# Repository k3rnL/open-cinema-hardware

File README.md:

# Open Cinema Hardware

Editable hardware for [Open Cinema](https://github.com/k3rnL/open-cinema). The [resources repository](https://github.com/k3rnL/open-cinema-resources) holds searchable knowledge and decision history.

## Current work: A12 routed ARC prototype

[Open A12](boards/rear-io-A12/README.md). ADV7511 ARC candidate → CS8416 four-source selector → three-pair LVDS link → Raspberry Pi. The Pi decodes/processes audio and sends output over USB to the amplifier. Optical ×2, coax, HDMI and six speaker pairs remain on one horizontal board.

- [Editable KiCad project](boards/rear-io-A12/rear-io-A12.kicad_pro) and [routed PCB](boards/rear-io-A12/rear-io-A12.kicad_pcb)
- [Schematic PDF](boards/rear-io-A12/exports/rear-io-A12-schematic.pdf)
- [Rigid STEP](boards/rear-io-A12/exports/rear-io-A12-rigid.step) / [Fusion archive](boards/rear-io-A12/exports/rear-io-A12-rigid.f3d)
- [Manufacturing review files](boards/rear-io-A12/manufacturing-review/README.md), [sourcing](boards/rear-io-A12/sourcing.md), [requirements](boards/rear-io-A12/requirements.md), [verification](boards/rear-io-A12/verification.md)

**Routing is complete: 0 ERC violations, 0 DRC violations and 0 unrouted connections. Manufacturing release remains on hold.** ARC-only/CEC startup, DD+ payload preservation and Pi capture have not been demonstrated; ADV7511 eligible supply and horizontal KLS speaker-clip current rating remain unresolved. The package includes Gerbers, drills, BOM/CPL, stackup and a [qualification plan](boards/rear-io-A12/bring-up.md); it is not an approved order.

The [accepted ARC scope](docs/arc-v1-requirements.md) defers eARC/lossless return audio while retaining DD+ Atmos as a validation target. A12 does not claim those tests passed.

## Mechanical integration

A12 preserves the 228 ×39.8 ×1.6 mm PCB, connector positions and four Ø3 holes at installation x±110 mm, depths 12/30 mm. Its rigid files contain one component with 162 solids and no child components; both reimports match. No owner backplate, L brackets or mains circuit is included.

The latest owner opening is 250 ×51 mm. Assembled clearance, airflow, cable access, tolerances and loaded thermal/EMI behavior remain to be checked. Exports retain the component-down installation datum, nominal z 67 mm. Existing owner CAD and the linked `rear-io-A5-assembly` cloud document were not saved or overwritten. Git publication does not update Fusion links automatically.

## Previous revisions

- [A11 ARC electrical study](boards/rear-io-A11/README.md): historical unrouted schematic/placement.
- [A10 electrical draft](boards/rear-io-A10/README.md): historical mux/LVDS design, HDMI unwired.
- [A9 mechanical baseline](docs/pcb-only-assembly-A9.md), [A8 horizontal study](docs/horizontal-assembly-A8.md).
- [Original mechanical KiCad project](boards/rear-io/rear-io.kicad_pro): manual edits preserved.
- [A7 vertical design in history](https://github.com/k3rnL/open-cinema-hardware/tree/eae54aa79c94255bdad5aaae5bf087d2b4166b0e).

JLCPCB is preferred; Global Sourcing/pre-order and external suppliers are allowed. No purchase or supplier contact was made. The saved A12 board owns routing; do not regenerate over manual work. [Checks and export reproduction](boards/rear-io-A12/verification.md).

No project hardware license has been selected. KiCad assets retain their [attribution/license](docs/sources/README.md).

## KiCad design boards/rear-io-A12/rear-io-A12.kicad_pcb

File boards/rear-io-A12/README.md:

# Rear I/O A12 — routed ARC prototype

2026-11-04. **Routing complete; manufacturing release on hold for qualification.**

A12 routes the ADV7511 ARC candidate, CS8416 four-source selector and three-pair LVDS transmitter. Audio decoding and processing remain on the Pi, with USB output to the amplifier. It adds a TPD1E10B06DYAR coaxial ESD clamp and completes the passive/header reference selections. This is an editable prototype, not a demonstrated ARC/DD+ product.

- [KiCad project](rear-io-A12.kicad_pro), [schematic](rear-io-A12.kicad_sch), [routed PCB](rear-io-A12.kicad_pcb).
- [Schematic PDF](exports/rear-io-A12-schematic.pdf), [front copper](exports/routing-front.svg), [back copper](exports/routing-back.svg).
- [Rigid STEP](exports/rear-io-A12-rigid.step) / [Fusion archive](exports/rear-io-A12-rigid.f3d) for enclosure integration.
- [Manufacturing review package](manufacturing-review/README.md), [requirements](requirements.md), [sourcing](sourcing.md), [verification](verification.md), [bring-up and release gates](bring-up.md).

## Routing and checks

Four copper layers: signal/power on both outer layers, continuous inner ground in the electronics region, plus outer ground fills and thermal/return vias. All 12 BTL speaker conductors have independent 2.5 mm paths on both outer layers with through-hole endpoints and no intervening vias. No speaker negative is tied to ground.

Final KiCad checks: **0 ERC violations, 0 DRC violations, 0 unrouted connections**. Separate schematic and board review passes check 423 electrical pad keys, 98 footprints and 92 resolved model links. These are static checks by one assistant, not independent engineer approval or powered testing. [Exact results and hashes](exports/review-two-passes.json).

The 228 × 39.8 × 1.6 mm outline, external connector positions and four Ø3 mounting holes remain unchanged from A9. The 250 × 51 mm owner opening still needs an assembled clearance/airflow check. No backplate, L brackets or mains circuit is included.

## Fusion integration

The STEP and F3D each contain **one component with 162 solid bodies and no child components**. Both reimports match their exported geometry. They use the previous component-down installation datum, nominal seating z 67 mm. Insert the entire component and joint a PCB mounting hole; disable Ground to Parent if needed. These files are separate integration exports. The existing linked Fusion cloud component and the owner's enclosure were not overwritten or saved.

## Why ordering remains on hold

ADV7511 procurement eligibility and ARC-only/DD+ operation remain unresolved. CEC firmware, Pi HAT/capture, speaker-clip current rating/supply, thermal/EMI/ESD behavior and assembled tolerances need qualification. Some CAD is generic library geometry or project reconstruction; it is not a guarantee of vendor tolerances. The Gerbers/BOM/CPL are supplied for engineering and supplier review, with an explicit hold notice. No supplier was contacted and no order was placed.

A11 remains historical. The routed PCB is the editable layout authority; do not rerun the A11 placement generator over it. See [reproduction instructions](verification.md).

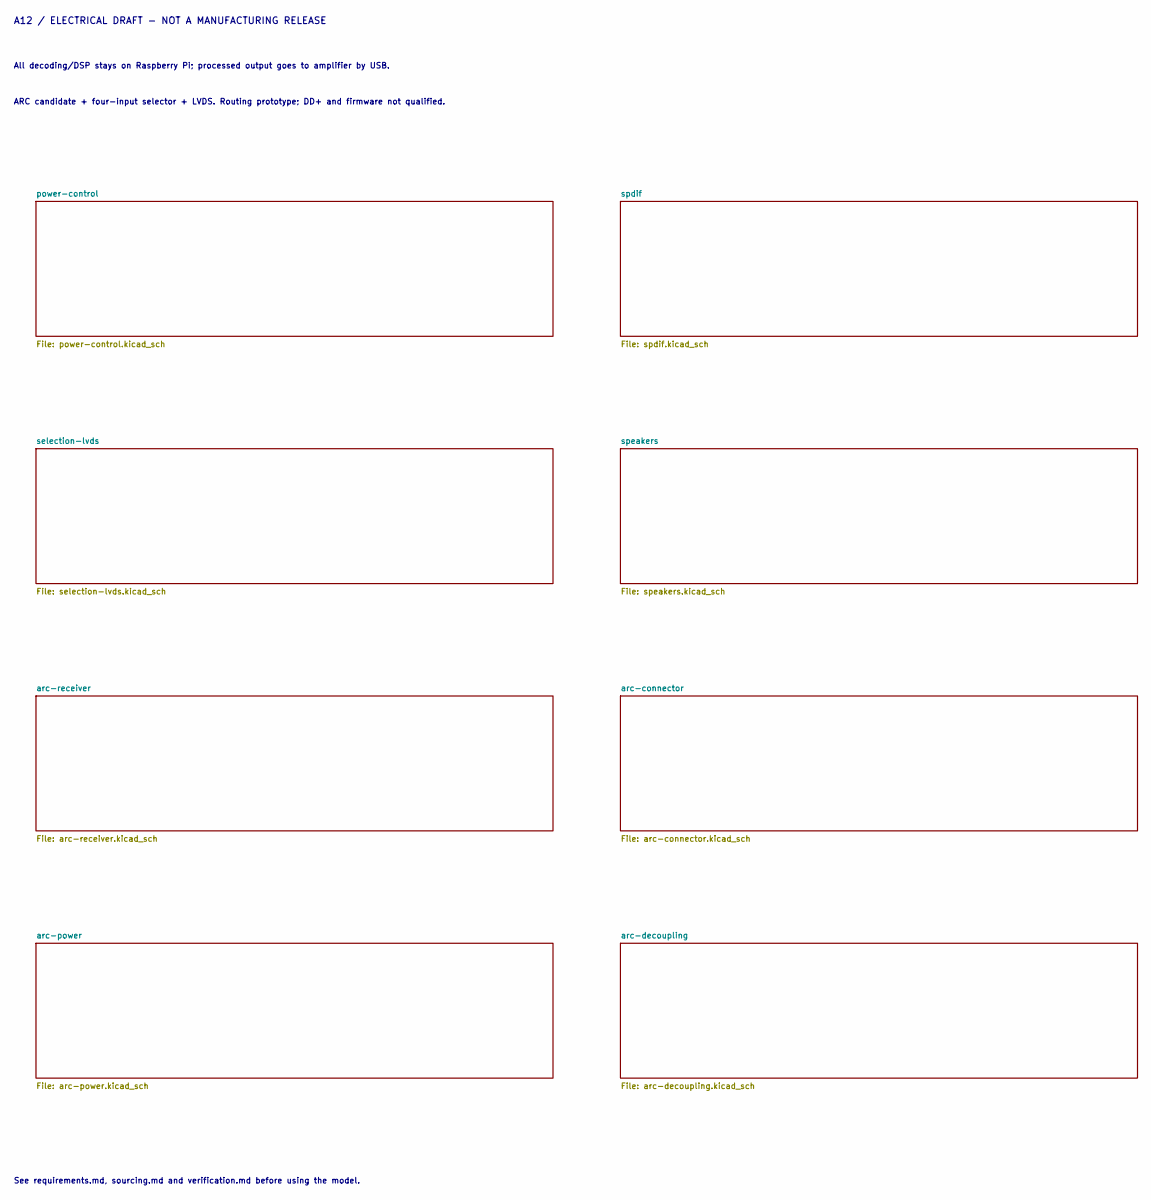
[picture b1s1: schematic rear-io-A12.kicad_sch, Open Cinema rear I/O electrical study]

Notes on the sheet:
A12 / ELECTRICAL DRAFT - NOT A MANUFACTURING RELEASE
All decoding/DSP stays on Raspberry Pi; processed output goes to amplifier by USB.
ARC candidate + four-input selector + LVDS. Routing prototype; DD+ and firmware not qualified.
See requirements.md, sourcing.md and verification.md before using the model.

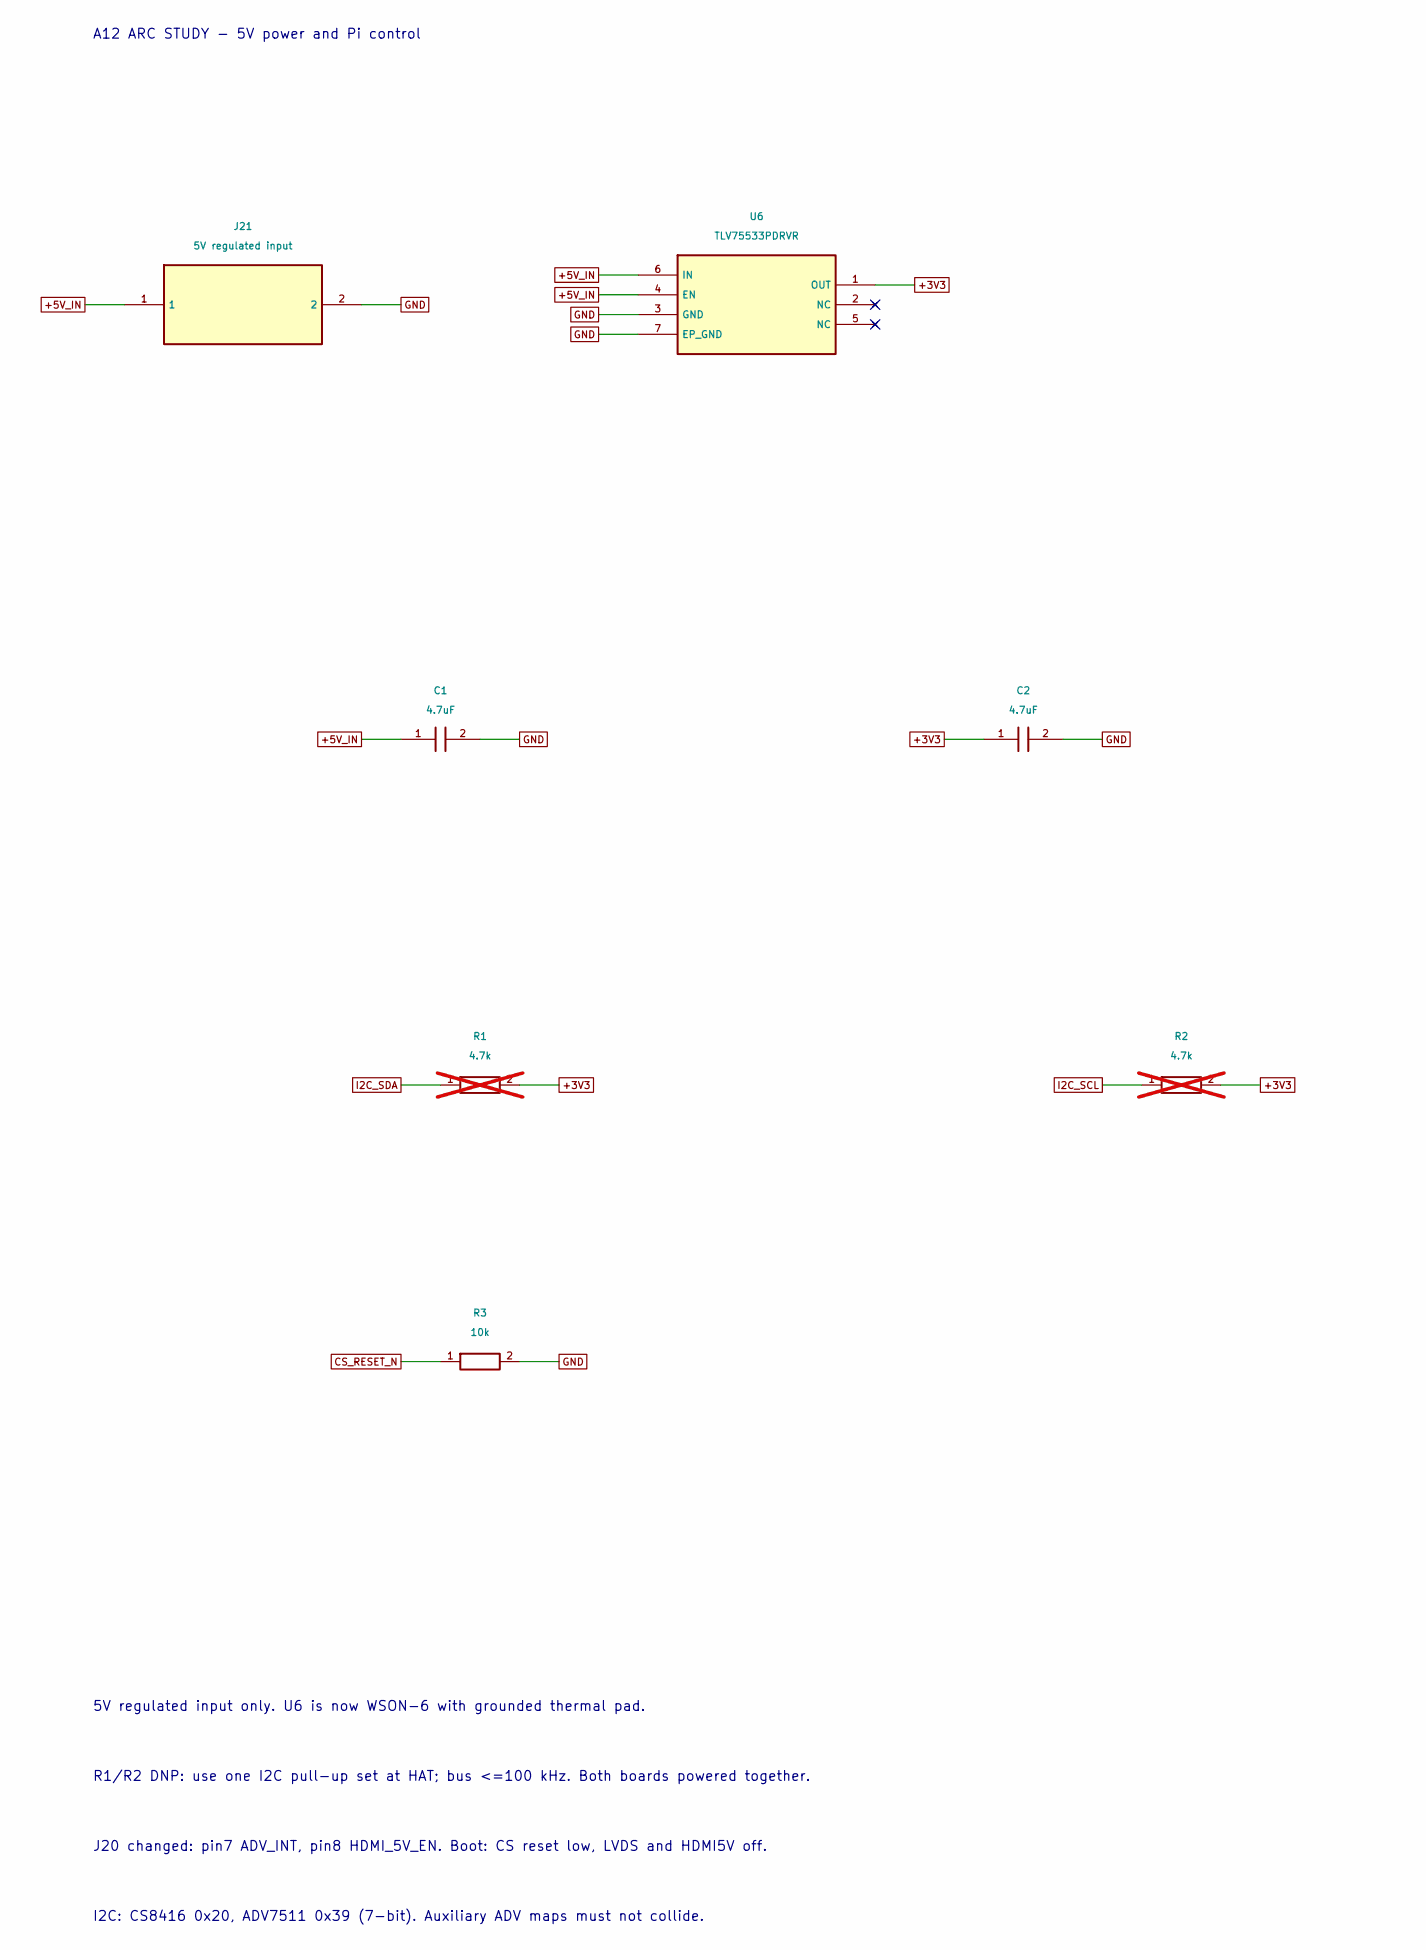
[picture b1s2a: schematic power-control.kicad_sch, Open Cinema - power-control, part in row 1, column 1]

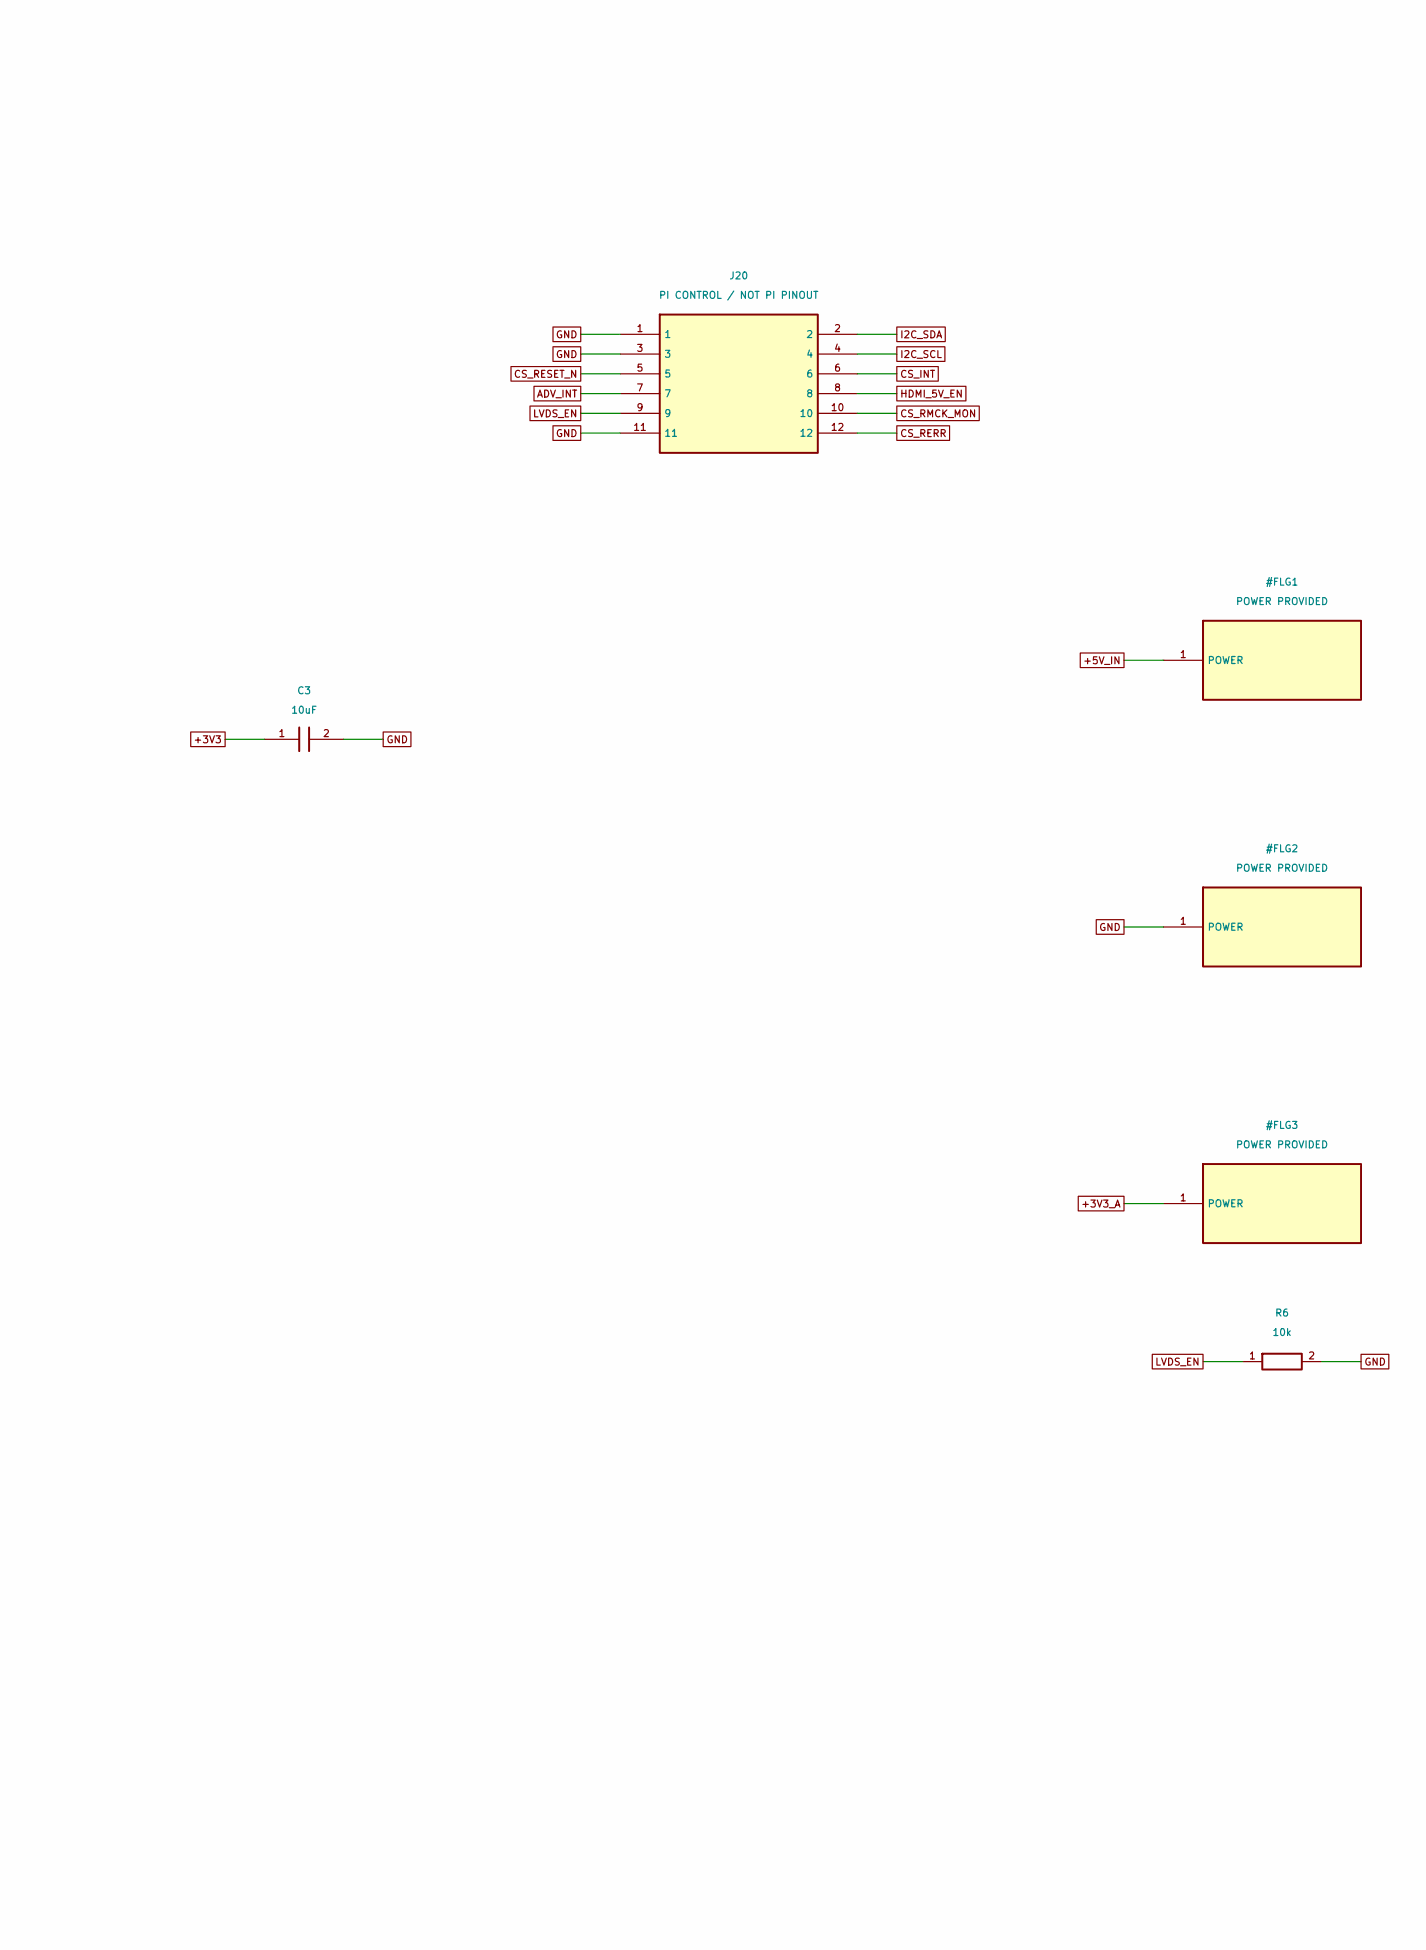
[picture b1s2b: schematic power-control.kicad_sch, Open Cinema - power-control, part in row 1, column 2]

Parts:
C1, C2: 4.7uF; C_0603_1608Metric; MPN CL10A475KO8NNNC
C3: 10uF; C_0603_1608Metric; MPN CL10A106KP8NNNC
J20: PI CONTROL / NOT PI PINOUT; PinHeader_2x06_P2.54mm_Vertical; MPN TSW-106-07-G-D
J21: 5V regulated input; PinHeader_1x02_P2.54mm_Vertical; MPN TSW-102-07-G-S
R1, R2: 4.7k; R_0603_1608Metric; MPN RC0603FR-074K7L; not fitted
R3, R6: 10k; R_0603_1608Metric; MPN RC0603FR-0710KL
U6: TLV75533PDRVR; WSON-6-1EP_2x2mm_P0.65mm_EP1x1.6mm; MPN TLV75533PDRVR

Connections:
+3V3: C2.1, C3.1, R1.2, R2.2, U6.1 (OUT); also elsewhere on the board
+5V_IN: C1.1, J21.1, U6.4 (EN), U6.6 (IN); also elsewhere on the board
ADV_INT: J20.7; also elsewhere on the board
CS_INT: J20.6; also elsewhere on the board
CS_RERR: J20.12; also elsewhere on the board
CS_RESET_N: J20.5, R3.1; also elsewhere on the board
CS_RMCK_MON: J20.10; also elsewhere on the board
GND: C1.2, C2.2, C3.2, J20.1, J20.3, J20.11, J21.2, R3.2, R6.2, U6.3 (GND), U6.7 (EP_GND); also elsewhere on the board
HDMI_5V_EN: J20.8; also elsewhere on the board
I2C_SCL: J20.4, R2.1; also elsewhere on the board
I2C_SDA: J20.2, R1.1; also elsewhere on the board
LVDS_EN: J20.9, R6.1; also elsewhere on the board

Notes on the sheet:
A12 ARC STUDY - 5V power and Pi control
5V regulated input only. U6 is now WSON-6 with grounded thermal pad.
R1/R2 DNP: use one I2C pull-up set at HAT; bus <=100 kHz. Both boards powered together.
J20 changed: pin7 ADV_INT, pin8 HDMI_5V_EN. Boot: CS reset low, LVDS and HDMI5V off.
I2C: CS8416 0x20, ADV7511 0x39 (7-bit). Auxiliary ADV maps must not collide.

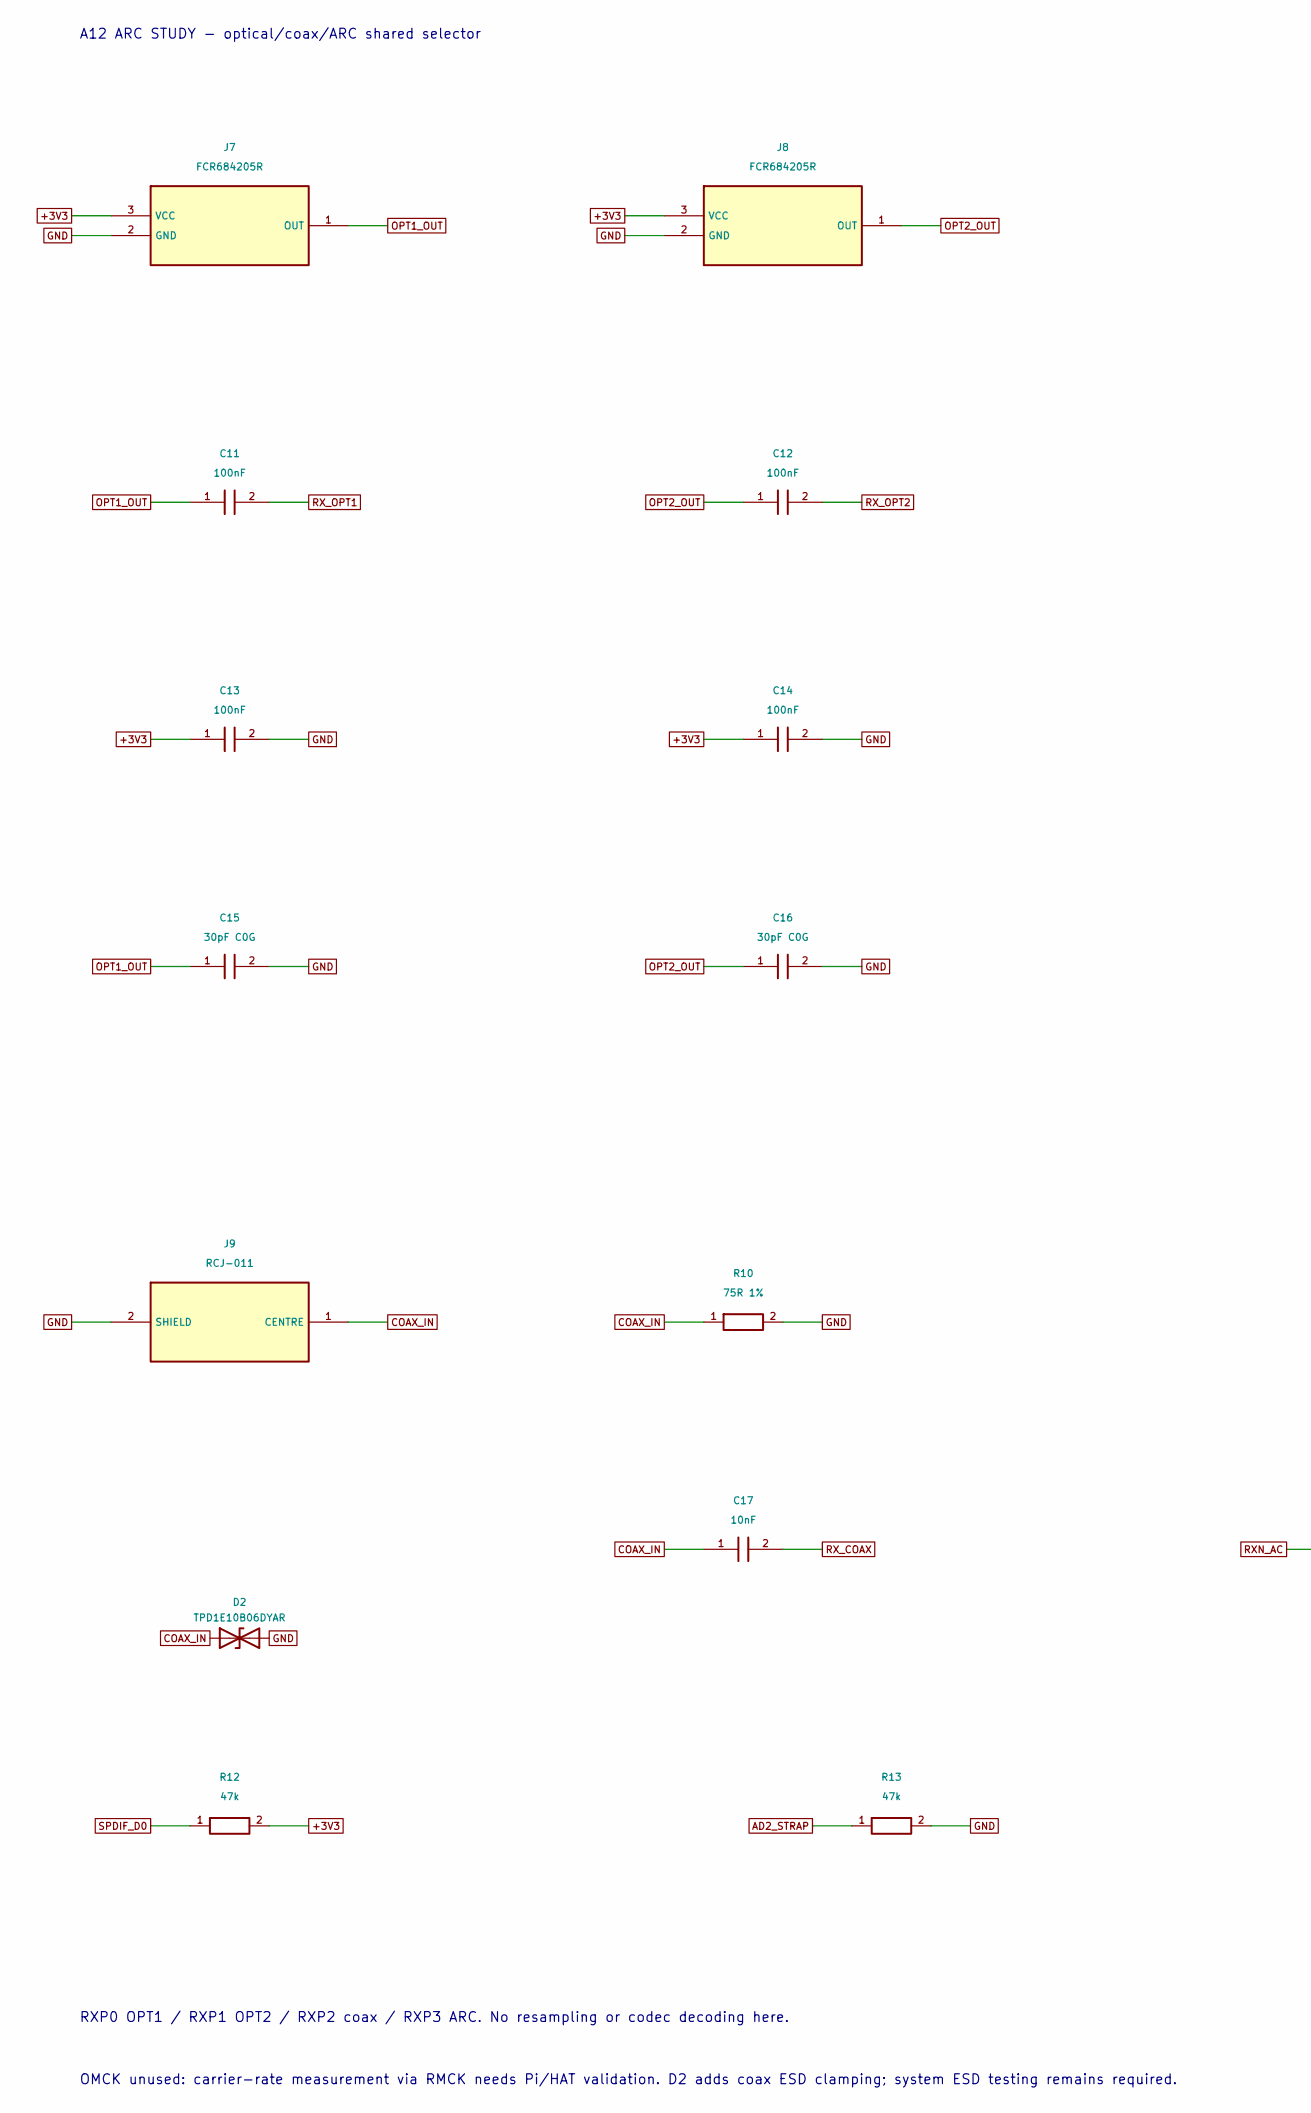
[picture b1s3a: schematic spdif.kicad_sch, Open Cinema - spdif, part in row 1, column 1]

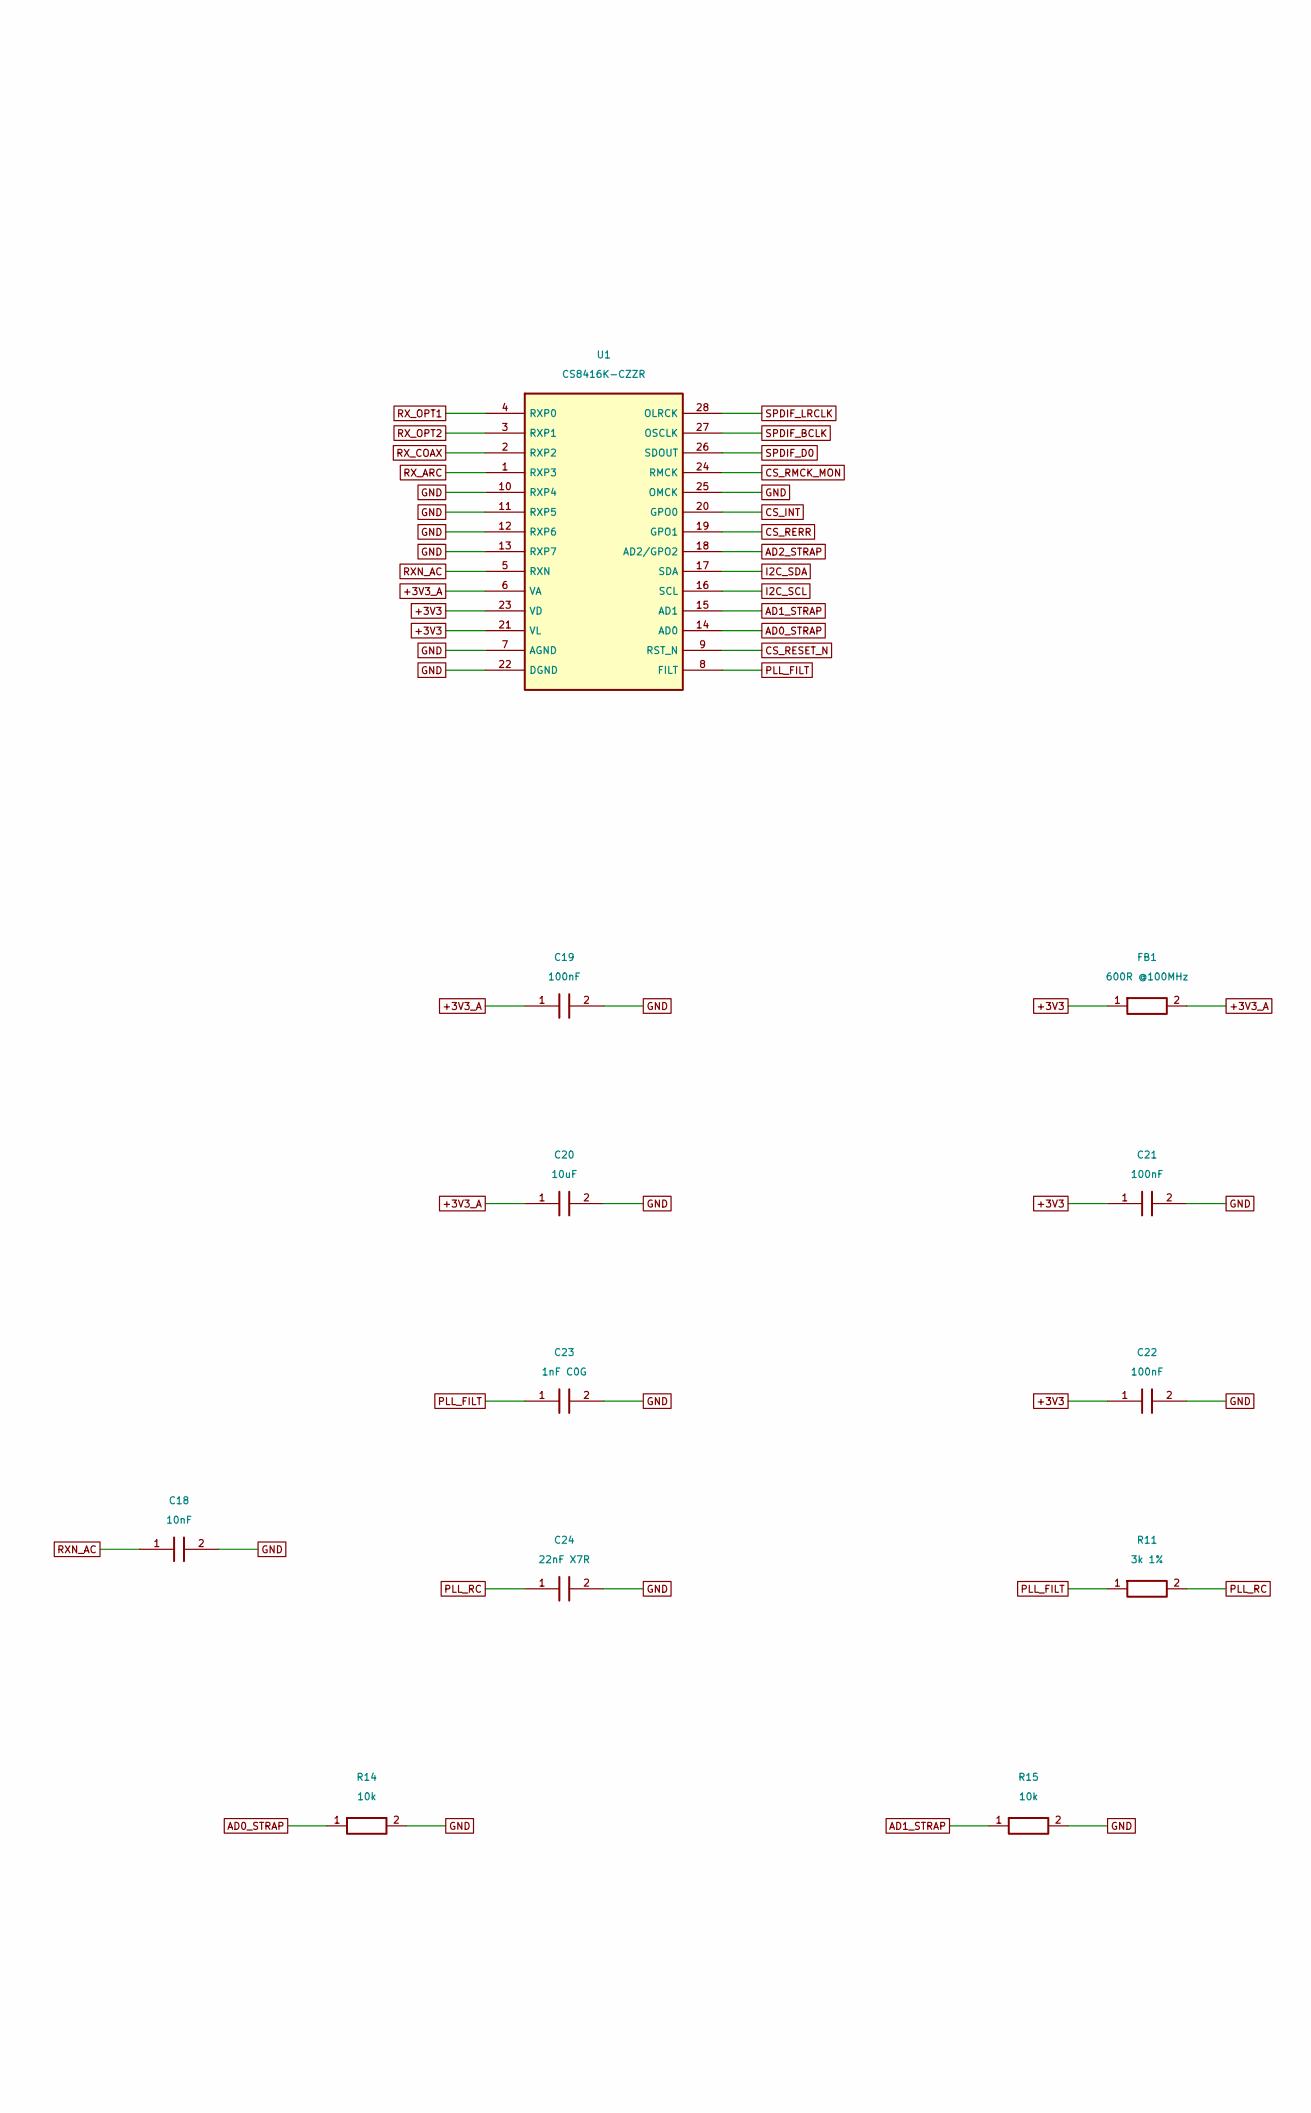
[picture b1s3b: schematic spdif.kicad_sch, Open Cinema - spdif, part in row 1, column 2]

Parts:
C11, C12, C13, C14, C19, C21, C22: 100nF; C_0603_1608Metric; MPN CL10B104KB8NNNC
C15, C16: 30pF C0G; C_0603_1608Metric; MPN CL10C300JB8NNNC
C17, C18: 10nF; C_0603_1608Metric; MPN CL10B103KB8NNNC
C20: 10uF; C_0603_1608Metric; MPN CL10A106KP8NNNC
C23: 1nF C0G; C_0603_1608Metric; MPN CL10C102JB8NNNC
C24: 22nF X7R; C_0603_1608Metric; MPN CL10B223KB8NNNC
D2: TPD1E10B06DYAR; D_SOD-523; MPN TPD1E10B06DYAR
FB1: 600R @100MHz; L_0603_1608Metric; MPN BLM18AG601SN1D
J7, J8: FCR684205R; Cliff_FCR684205R; MPN FCR684205R
J9: RCJ-011; SameSky_RCJ_011_Horizontal_A8; MPN RCJ-011
R10: 75R 1%; R_0603_1608Metric; MPN RC0603FR-0775RL
R11: 3k 1%; R_0603_1608Metric; MPN RC0603FR-073KL
R12, R13: 47k; R_0603_1608Metric; MPN RC0603FR-0747KL
R14, R15: 10k; R_0603_1608Metric; MPN RC0603FR-0710KL
U1: CS8416K-CZZR; TSSOP-28_4.4x9.7mm_P0.65mm; MPN CS8416K-CZZR

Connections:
+3V3: C13.1, C14.1, C21.1, C22.1, FB1.1, J7.3 (VCC), J8.3 (VCC), R12.2, U1.21 (VL), U1.23 (VD); also elsewhere on the board
+3V3_A: C19.1, C20.1, FB1.2, U1.6 (VA)
AD0_STRAP: R14.1, U1.14 (AD0)
AD1_STRAP: R15.1, U1.15 (AD1)
AD2_STRAP: R13.1, U1.18 (AD2/GPO2)
COAX_IN: C17.1, D2.1 (A1), J9.1 (CENTRE), R10.1
CS_INT: U1.20 (GPO0); also elsewhere on the board
CS_RERR: U1.19 (GPO1); also elsewhere on the board
CS_RESET_N: U1.9 (RST_N); also elsewhere on the board
CS_RMCK_MON: U1.24 (RMCK); also elsewhere on the board
GND: C13.2, C14.2, C15.2, C16.2, C18.2, C19.2, C20.2, C21.2, C22.2, C23.2, C24.2, D2.2 (A2), J7.2 (GND), J8.2 (GND), J9.2 (SHIELD), R10.2, R13.2, R14.2, R15.2, U1.7 (AGND), U1.10 (RXP4), U1.11 (RXP5), U1.12 (RXP6), U1.13 (RXP7), U1.22 (DGND), U1.25 (OMCK); also elsewhere on the board
I2C_SCL: U1.16 (SCL); also elsewhere on the board
I2C_SDA: U1.17 (SDA); also elsewhere on the board
OPT1_OUT: C11.1, C15.1, J7.1 (OUT)
OPT2_OUT: C12.1, C16.1, J8.1 (OUT)
PLL_FILT: C23.1, R11.1, U1.8 (FILT)
PLL_RC: C24.1, R11.2
RXN_AC: C18.1, U1.5 (RXN)
RX_ARC: U1.1 (RXP3); also elsewhere on the board
RX_COAX: C17.2, U1.2 (RXP2)
RX_OPT1: C11.2, U1.4 (RXP0)
RX_OPT2: C12.2, U1.3 (RXP1)
SPDIF_BCLK: U1.27 (OSCLK); also elsewhere on the board
SPDIF_D0: R12.1, U1.26 (SDOUT); also elsewhere on the board
SPDIF_LRCLK: U1.28 (OLRCK); also elsewhere on the board

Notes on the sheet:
A12 ARC STUDY - optical/coax/ARC shared selector
RXP0 OPT1 / RXP1 OPT2 / RXP2 coax / RXP3 ARC. No resampling or codec decoding here.
OMCK unused: carrier-rate measurement via RMCK needs Pi/HAT validation. D2 adds coax ESD clamping; system ESD testing remains required.

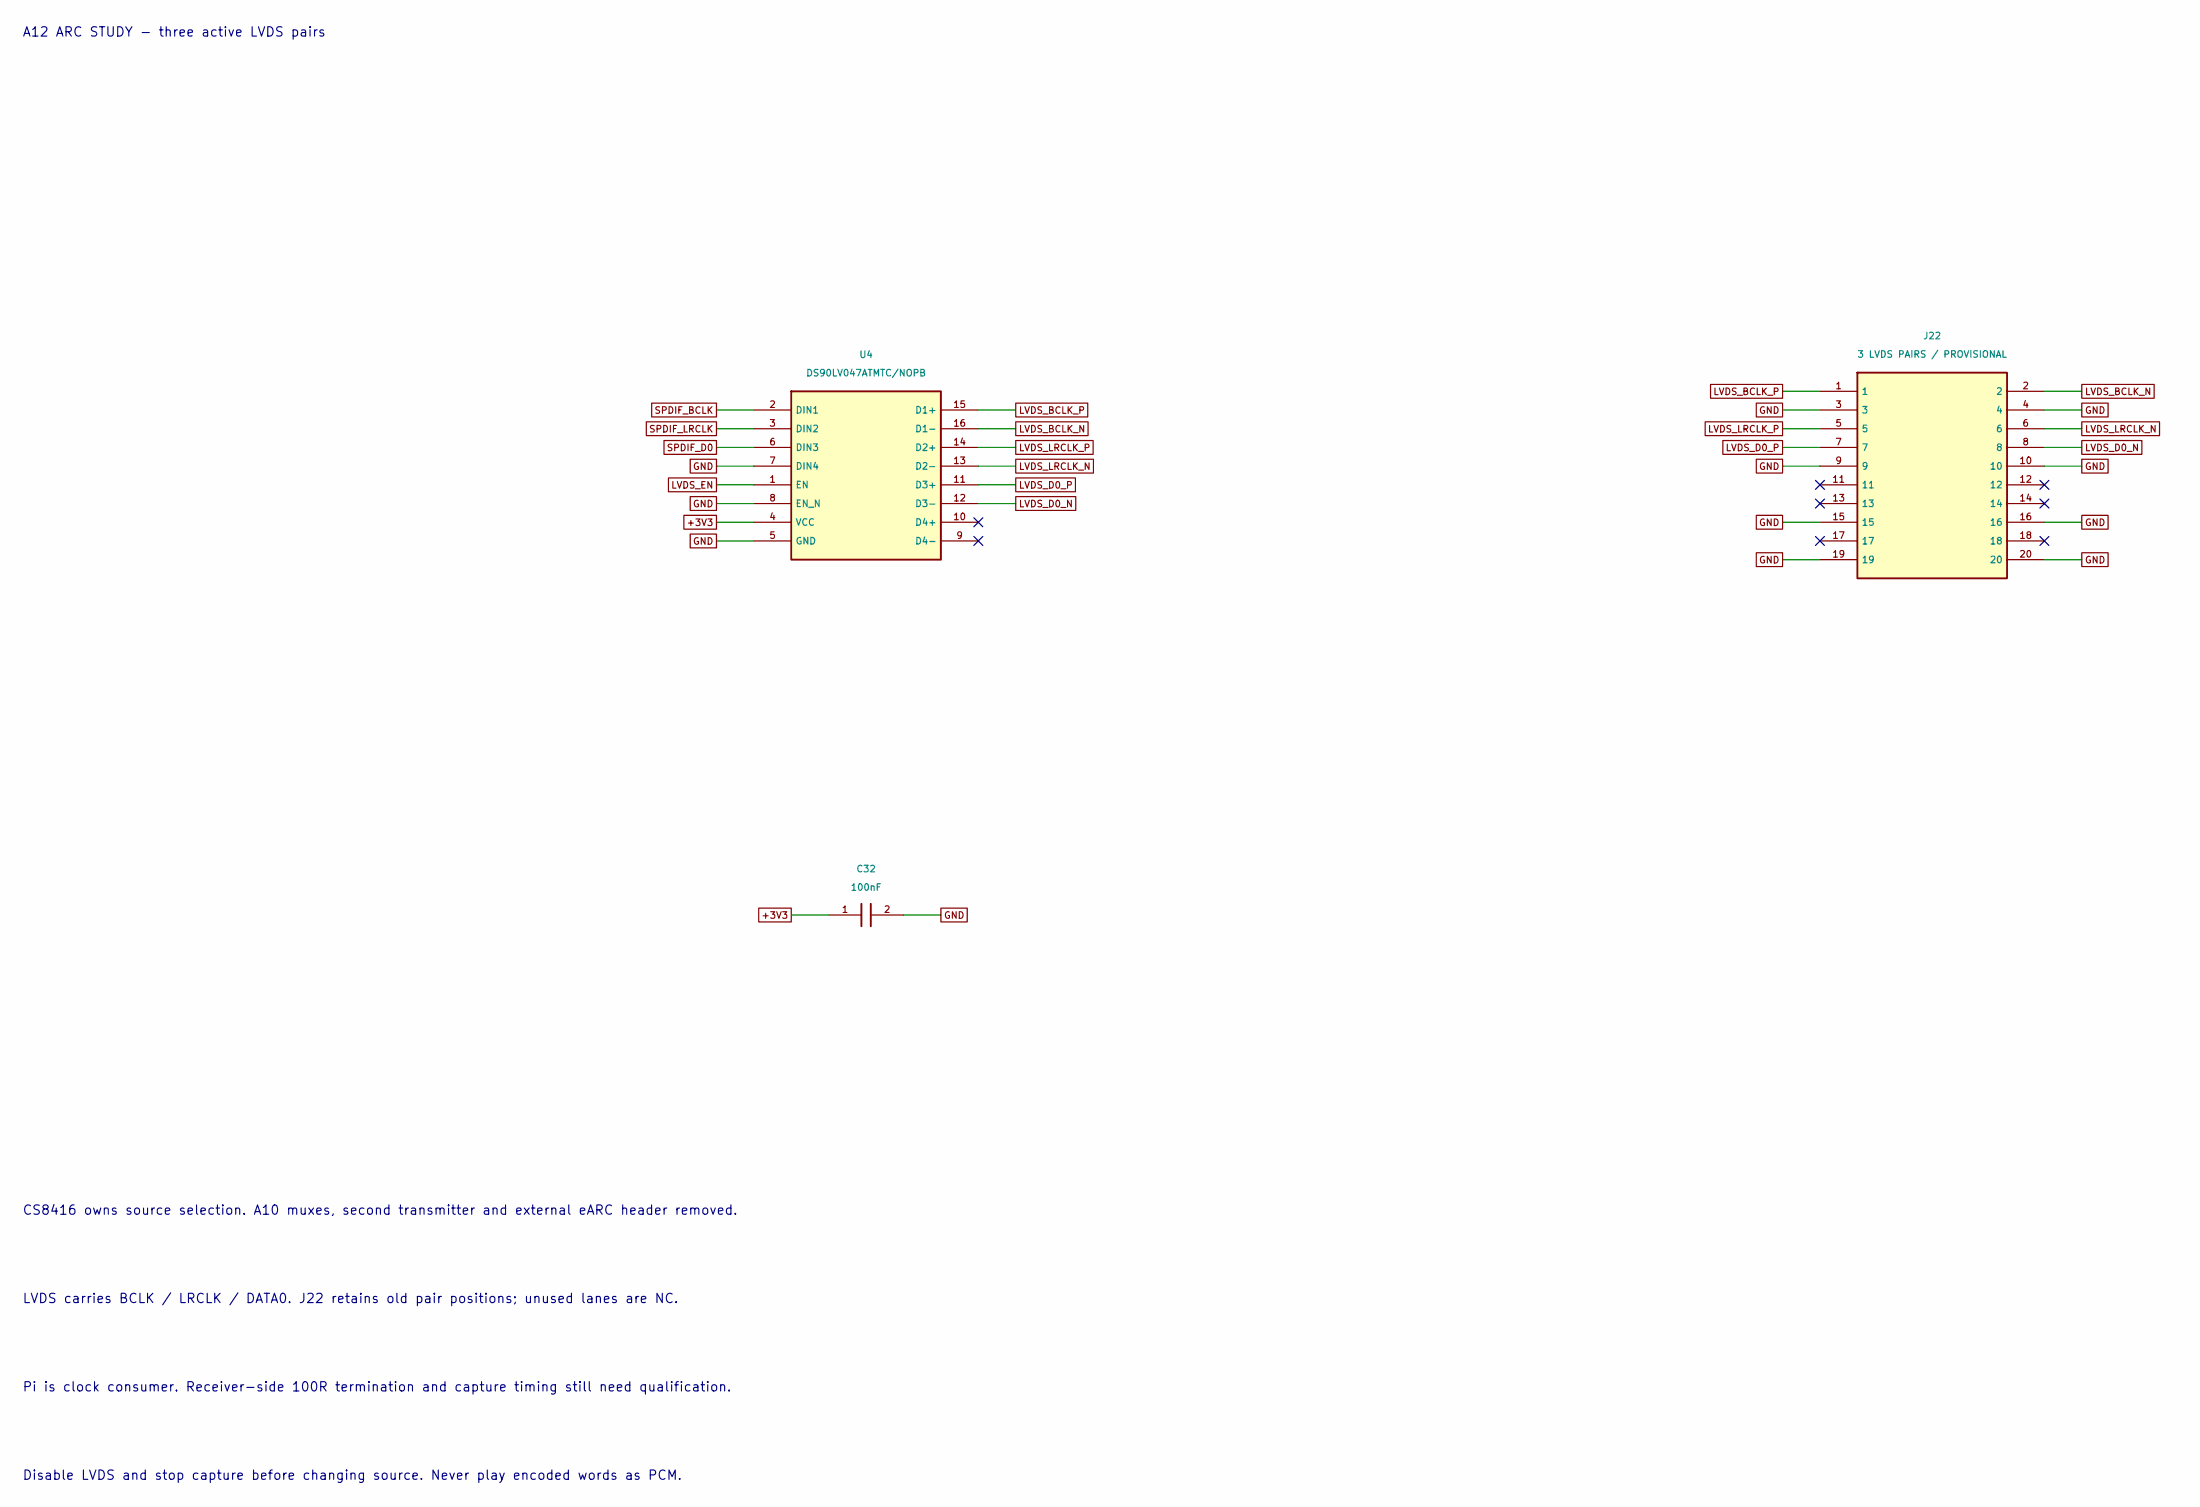
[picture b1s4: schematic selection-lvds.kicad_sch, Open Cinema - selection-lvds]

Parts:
C32: 100nF; C_0603_1608Metric; MPN CL10B104KB8NNNC
J22: 3 LVDS PAIRS / PROVISIONAL; PinHeader_2x10_P2.54mm_Vertical; MPN TSW-110-07-G-D
U4: DS90LV047ATMTC/NOPB; TSSOP-16_4.4x5mm_P0.65mm; MPN DS90LV047ATMTC/NOPB

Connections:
+3V3: C32.1, U4.4 (VCC); also elsewhere on the board
GND: C32.2, J22.3, J22.4, J22.9, J22.10, J22.15, J22.16, J22.19, J22.20, U4.5 (GND), U4.7 (DIN4), U4.8 (EN_N); also elsewhere on the board
LVDS_BCLK_N: J22.2, U4.16 (D1-)
LVDS_BCLK_P: J22.1, U4.15 (D1+)
LVDS_D0_N: J22.8, U4.12 (D3-)
LVDS_D0_P: J22.7, U4.11 (D3+)
LVDS_EN: U4.1 (EN); also elsewhere on the board
LVDS_LRCLK_N: J22.6, U4.13 (D2-)
LVDS_LRCLK_P: J22.5, U4.14 (D2+)
SPDIF_BCLK: U4.2 (DIN1); also elsewhere on the board
SPDIF_D0: U4.6 (DIN3); also elsewhere on the board
SPDIF_LRCLK: U4.3 (DIN2); also elsewhere on the board

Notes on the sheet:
A12 ARC STUDY - three active LVDS pairs
CS8416 owns source selection. A10 muxes, second transmitter and external eARC header removed.
LVDS carries BCLK / LRCLK / DATA0. J22 retains old pair positions; unused lanes are NC.
Pi is clock consumer. Receiver-side 100R termination and capture timing still need qualification.
Disable LVDS and stop capture before changing source. Never play encoded words as PCM.
